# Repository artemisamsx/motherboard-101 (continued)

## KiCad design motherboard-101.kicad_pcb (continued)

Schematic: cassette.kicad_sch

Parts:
C22: 100nF; Disc_capacitor
C32, C35: 1uF; Radial_capacitor
C33, C34: 22nF; Disc_capacitor
D3: 1N4448; Axial_diode
J8: DIN8
K1: Relay
Q2: 2N2907; TO92
R13: 2k2; Axial_resistor
R14, R15, R17: 4k7; Axial_resistor
R16: 100; Axial_resistor
R18: 220k; Axial_resistor
R19: 1k; Axial_resistor
R20: 10k; Axial_resistor
R21, R22: 2k7; Axial_resistor
U19: LM311; DIP-8_300

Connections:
/CASIN: R19.1, U19.7 (COLOUT); also elsewhere on the board
/CASOUT: C32.1; also elsewhere on the board
/~CASMOTOR: R13.2; also elsewhere on the board
GND: C22.2, C33.2, C35.2, J8.1, J8.2, J8.3, J8.8, Q2.1 (1C), R16.1, R22.1, U19.1 (EMITOUT), U19.4 (GND); also elsewhere on the board
unnamed: C32.2, R14.2
unnamed: C33.1, R14.1, R15.2
unnamed: C34.1, R17.1
unnamed: C34.2, J8.5
unnamed: C35.1, R20.2, R21.1, R22.2, U19.2 (IN+)
unnamed: D3.1, K1.2, Q2.3 (E)
unnamed: J8.4, R15.1, R16.2
unnamed: J8.6, K1.4
unnamed: J8.7, K1.3
unnamed: Q2.2 (B), R13.1
unnamed: R17.2, R18.1, R20.1, U19.3 (IN-)
~: C22.1, D3.2, K1.1, R18.2, R19.2, R21.2, U19.8 (VCC); also elsewhere on the board

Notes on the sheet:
Cassette in (read)
Cassette out (write)
REM+
REM-

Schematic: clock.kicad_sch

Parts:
C20: 100nF; Disc_capacitor
C36, C37: (no value)
R23: 1M; Axial_resistor
R24: 1K; Axial_resistor
U9: 74HCU04; DIP-14_300
U17: 74HC74; DIP-14_300
Y1: 3.58Mhz; Crystal

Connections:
/CLK: U9.12, U17.3 (CP); also elsewhere on the board
/PSGCLK: U17.5 (Q); also elsewhere on the board
GND: C20.2, C36.2, C37.2, U17.7 (GND); also elsewhere on the board
unnamed: C36.1, R23.1, U9.9, Y1.1
unnamed: C37.1, R24.1, Y1.2
unnamed: R23.2, R24.2, U9.8, U9.11
unnamed: U9.10, U9.13
unnamed: U17.2 (D), U17.6 (~Q)
~: C20.1, U17.1 (~RD), U17.4 (~SD), U17.14 (VCC); also elsewhere on the board

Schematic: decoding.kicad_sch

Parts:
C8, C10, C11, C12, C13, C38: 100nF; Disc_capacitor
U10: 74HC04; DIP-14_300
U11, U12, U13: 74HC32; DIP-14_300
U14: 74HC08; DIP-14_300
U15: 74HC139; DIP-16_300
U17: 74HC74; DIP-14_300
U26: 74HC138; DIP-16_300

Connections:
/ADDR0: U11.9; also elsewhere on the board
/ADDR1: U10.3, U11.13; also elsewhere on the board
/ADDR14: U15.14 (A0); also elsewhere on the board
/ADDR15: U10.1, U11.2, U15.13 (A1); also elsewhere on the board
/CPU/ADDR3: U26.1 (A0); also elsewhere on the board
/CPU/ADDR4: U26.2 (A1); also elsewhere on the board
/CPU/ADDR5: U26.3 (A3); also elsewhere on the board
/CPU/ADDR6: U13.2; also elsewhere on the board
/CPU/ADDR7: U10.9; also elsewhere on the board
/DATADIR: U14.3; also elsewhere on the board
/DECODING/~PPISL: U12.5, U12.9, U17.10 (~SD), U26.10 (~Y5)
/DECODING/~PSGBDIR: U10.13, U11.11, U14.10
/DECODING/~PSGRD: U13.5, U13.8
/DECODING/~PSGSL: U13.10, U13.12, U26.11 (~Y4)
/DECODING/~PSGWR: U11.12, U13.11
/PSGBC1: U10.10; also elsewhere on the board
/PSGBDIR: U10.12; also elsewhere on the board
/~CS1: U14.4, U15.11 (~Y1); also elsewhere on the board
/~CS2: U14.5, U15.10 (~Y2); also elsewhere on the board
/~CS12: U14.6; also elsewhere on the board
/~IORQ: U12.1, U26.5 (~E2); also elsewhere on the board
/~M1: U12.2, U26.6 (E3); also elsewhere on the board
/~MREQ: U12.12; also elsewhere on the board
/~PPIRD: U12.6; also elsewhere on the board
/~PPIRDY: U17.8 (~Q); also elsewhere on the board
/~PPIWR: U12.8; also elsewhere on the board
/~RAMSL0: U11.6; also elsewhere on the board
/~RAMSL1: U11.3; also elsewhere on the board
/~RD: U12.4, U13.9, U14.1, U15.15 (~OE); also elsewhere on the board
/~RESET: U17.13 (~RD); also elsewhere on the board
/~RFSH: U10.5; also elsewhere on the board
/~SLTSL1: U11.1, U11.4; also elsewhere on the board
/~SLTSLEN: U12.11; also elsewhere on the board
/~VDPSL: U26.12 (~Y3); also elsewhere on the board
/~WR: U12.10, U13.13; also elsewhere on the board
GND: C8.2, C10.2, C11.2, C12.2, C13.2, C38.2, U10.7 (GND), U11.7 (GND), U12.7 (GND), U13.7 (GND), U14.7 (GND), U17.11 (CP), U17.12 (D), U26.8 (GND); also elsewhere on the board
unnamed: U10.2, U11.5
unnamed: U10.4, U13.4
unnamed: U10.6, U12.13
unnamed: U10.8, U13.1
unnamed: U10.11, U11.8
unnamed: U11.10, U14.8
unnamed: U12.3, U14.2
unnamed: U13.3, U26.4 (~E1)
unnamed: U13.6, U14.9
~: C8.1, C10.1, C11.1, C12.1, C13.1, C38.1, U10.14 (VCC), U11.14 (VCC), U12.14 (VCC), U13.14 (VCC), U14.14 (VCC), U26.16 (VCC); also elsewhere on the board

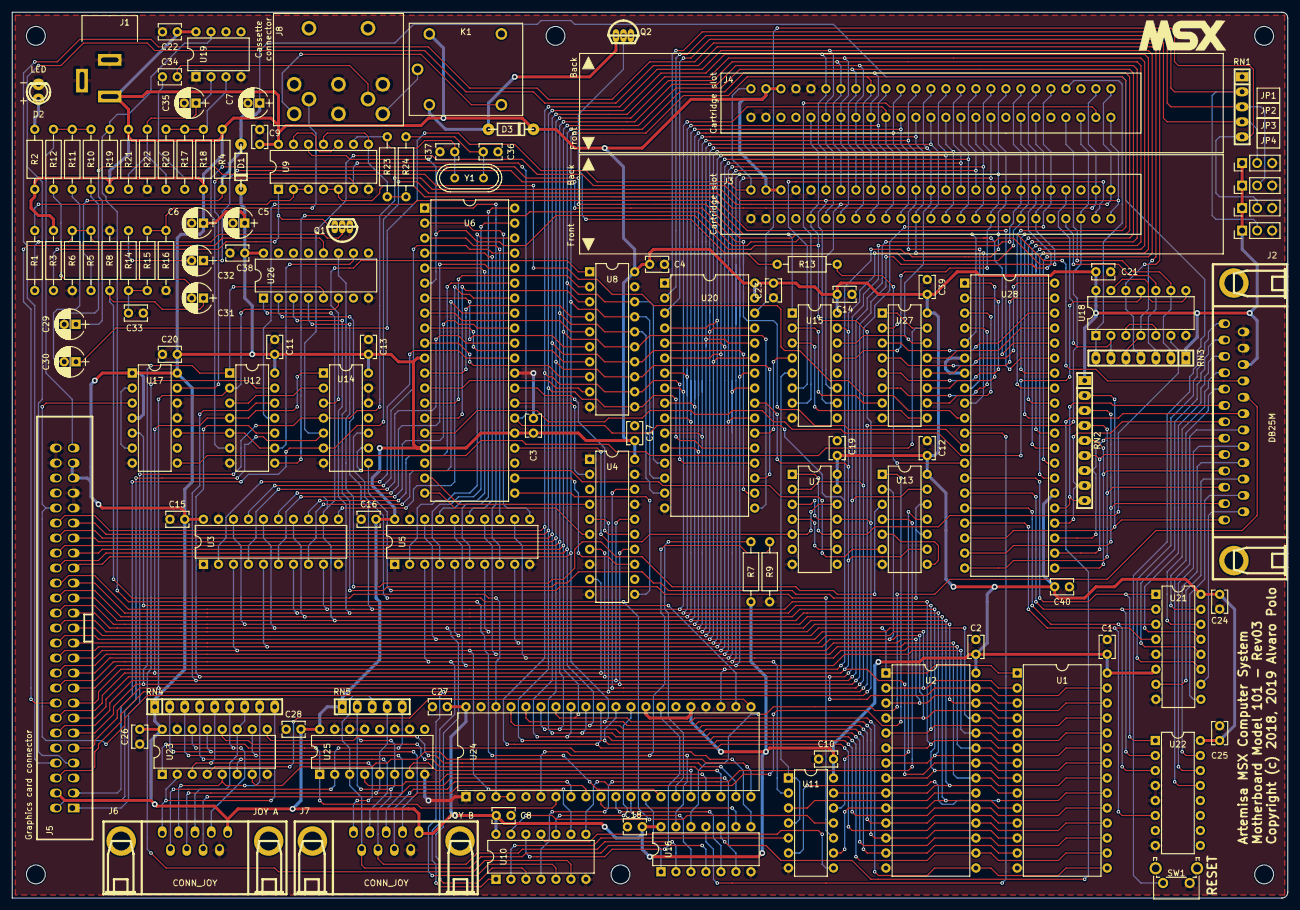
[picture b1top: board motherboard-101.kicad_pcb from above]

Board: 2 copper layers, 216.0 x 150.0 mm, 117 parts (0 on the bottom side), 207 nets.

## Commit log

2020-05-17 Rename motherboard project to model 101
2021-03-23 Use kicadlibs as submodule
2021-03-23 Add README and LICENSE files
2021-03-23 Add gitignore file
2021-04-12 Fix wrong location of Artemisa libraries
2021-04-12 Update libraries
2021-04-12 Fix wrong location of relay 3D model
2021-04-13 Update plot properties
2021-04-13 Move decoupling capacitors out from power sheet
    Put them where the first part of the IC is used.
2021-04-14 Update 7404 parts to have the power pins in the first unit
2021-04-15 Update 7408 parts to have the power pins in the first unit
2021-04-15 Update 74139 parts to have the power pins in the first unit
2021-08-11 Unknown changes to power.sch
2021-08-11 Update 7474 parts to have the power pins in the first unit
2022-04-28 Upgrade project files to KiCad 6
2024-01-18 Fix wrong cap type in clock generator
    Also fill some references automatically generated by KiCAD.
2024-08-26 Upgrade project files to KiCad v8
